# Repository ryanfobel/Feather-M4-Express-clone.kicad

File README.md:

# Feather-M4-Express-PCB-clone
KiCad version of Adafruit's [Feather M4 Express PCB](https://github.com/adafruit/Adafruit-Feather-M4-Express-PCB)
design files. Conversion from Eagle was performed using [these eagle-to-kicad scripts](https://github.com/lachlanA/eagle-to-kicad).

For more details on Adafruit's Feather M4 Express, check out the product pages at

   * https://www.adafruit.com/products/3857

Adafruit invests time and resources providing this open source design, 
please support Adafruit and open-source hardware by purchasing 
products from Adafruit!

Designed by Adafruit Industries.  
Creative Commons Attribution, Share-Alike license, check license.txt for more information.  
All text above must be included in any redistribution.  
Conversion from Eagle to KiCad by Ryan Fobel.

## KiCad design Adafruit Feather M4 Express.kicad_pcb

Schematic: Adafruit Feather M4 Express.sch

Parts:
C2, C4: 22pF; MICROBUILDER_0603-NO; MPN C0201C220K3GACTU
C3, C6, C8: 10~F; MICROBUILDER_0805-NO; MPN C0805C106K8PACTU
C5, C13: 10uF; MICROBUILDER_0805-NO; MPN C0805C106K8PACTU
C7, C10, C11, C12, C14, C15: 1uF; MICROBUILDER_0603-NO; MPN CL10B105KP8NNNC
CHG40: ORANGE; MICROBUILDER_CHIPLED_0805_NOOUTLINE; MPN LTST-C170KFKT
D4: MBR120; MICROBUILDER_SOD-123; MPN MBR120VLSFT3G
D+40: TPB1,27; TESTPAD_B1_27
D-40: TPB1,27; TESTPAD_B1_27
JP1: MICROBUILDER_1X16_ROUND
JP2, JP4: GROVE_HEADER_1X4; GROVE_HEADER_1x4
JP3: MICROBUILDER_1X12_ROUND
L2: 10uH; MICROBUILDER_INDUCTOR_1007; MPN LBR2518T100K
L40: RED; MICROBUILDER_CHIPLED_0805_NOOUTLINE; MPN 150060RS75000
LED1: WS2812B3535; MICROBUILDER_LED3535; MPN WS2812B3535
Q3: DMG341; MICROBUILDER_SOT23-R; MPN DMG3413L-7
R2: 1K; MICROBUILDER_0603-NO; MPN CRCW02011K00JNED
R3, R4, R5, R6, R8: 10K; MICROBUILDER_0603-NO; MPN ERJ-3GEYJ103V
R7: 2.2K; MICROBUILDER_0603-NO; MPN ERJ-3GEYJ222V
R9: 100K; MICROBUILDER_RESPACK_4X0603_NO; MPN ESR03EZPJ104
SJ1: MICROBUILDER_SOLDERJUMPER_CLOSEDWIRE
SW1: KMR2; MICROBUILDER_BTN_KMR2_4.6X2.8; MPN KMR231NG LFS
TP1, TP2: MICROBUILDER_TESTPOINT_ROUND_1.5MM
U1: 2MB Flash; MICROBUILDER_USON8; MPN GD25Q16CTIGR
U2: AP2112-3.3; MICROBUILDER_SOT23-5; MPN AP2112K-3.3TRG1
U3: MCP73831T-2ACI/OT; MICROBUILDER_SOT23-5; MPN MCP73831T-2ACI/OT
U$14: ATSAMD51J; MICROBUILDER_PQFN64-1; MPN ATSAMD51G19A-MU
VP_0, VP_1, VP_2, VP_3, VP_4, VP_5, VP_6, VP_7, VP_8, VP_9, VP_10, VP_11, VP_12: VPDEV0; VPAD_VPAC0
VP_13, VP_14, VP_15, VP_16, VP_17, VP_18, VP_19, VP_20, VP_21, VP_22, VP_23, VP_24, VP_25, VP_26, VP_27, VP_31, VP_32: VPDEV1; VPAD_VPAC1
VP_28, VP_29, VP_30, VP_33, VP_34, VP_35, VP_36, VP_37, VP_38, VP_39, VP_40, VP_41, VP_42, VP_43, VP_44, VP_45, VP_46, VP_47, VP_48, VP_49, VP_50, VP_51, VP_52, VP_53, VP_54, VP_55, VP_56, VP_57: VPDEV2; VPAD_VPAC2
X1: JSTPH; MICROBUILDER_JSTPH2; MPN S2B-PH-SM4-TB(LF)(SN)
X2: 32.768; ADAFRUIT2_XTAL3215; MPN LFXTAL009678REEL
X3: microUSB; MICROBUILDER_4UCONN_20329_V2; MPN 10118194-0001LF

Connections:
+3V3: C5.1, C7.1, C8.1, C10.1, C11.1, JP1.15, JP2.3, JP4.3, LED1.2 (VDD), R4.1, R5.2, R6.1, SJ1.2, U1.8 (VCC), U2.5 (OUT), U$14.8 (VDDANA), U$14.16 (PA07/I7/AIN7/SERCOM0.3), U$14.21 (VDDIO_0), U$14.34 (VDDIO_1), U$14.48 (VDDIO_2), U$14.56 (VDDIO_3)
A0: JP1.12, JP2.1, U$14.3 (PA02/EINT2/AIN0/VOUT0)
A1: JP1.11, JP2.2, U$14.14 (PA05/I5/AIN5/VOUT1/SERCOM0.1)
A2: JP1.10, U$14.11 (PB08/I8/AIN2/SERCOM4.0)
A3: JP1.9, U$14.12 (PB09/I9/AIN3/SERCOM4.1)
A4: JP1.8, U$14.13 (PA04/I4/VREFB/AIN4/SERCOM0.0)
A5: JP1.7, U$14.15 (PA06/I6/VREFC/AIN6/SERCOM0.2)
AREF: C14.1, JP1.14, SJ1.1, U$14.4 (PA03/I3/VREFA/AIN1)
D4: JP1.1, U$14.31 (PA14/I14/SERCOM2+4.2)
D5: JP3.10, U$14.35 (PA16/I2C/I0/SERCOM1.0+3.1)
D6: JP3.9, U$14.37 (PA18/I2/SERCOM1+3.2)
D8_NEOPIX: LED1.1 (DI), U$14.64 (PB03/I3/AIN15/SERCOM5.1)
D9: JP3.8, U$14.38 (PA19/I3/SERCOM1+3.3)
D10: JP3.7, U$14.41 (PA20/I4/SERCOM3+5.2/I2SFS0)
D11: JP3.6, U$14.42 (PA21/I5/SERCOM3+5.3/I2SDO)
D12: JP3.5, U$14.43 (PA22/I2C/16/SERCOM3.0+5.1/I2SDI)
D13: JP3.4, R7.1, U$14.44 (PA23/I2C/I7/SERCOM3.1+5.0/SOF/I2SFS1)
D+: D+40.TP, U$14.46 (PA25/19/SERCOM3+5.3/D+), X3.D+
D-: D-40.TP, U$14.45 (PA24/I8/SERCOM3+5.2/D-), X3.D-
EN: JP3.2, R3.1, U2.3 (EN)
GND: C2.2, C3.2, C4.2, C5.2, C6.2, C7.2, C8.2, C10.2, C11.2, C12.1, C13.2, C14.2, C15.2, JP1.13, JP2.4, JP4.4, L40.C, LED1.4 (GND), R8.2, R9.3 (1), R9.7 (2), SW1.B (S), SW1.B' (S1), U1.4 (VSS), U2.2 (GND), U3.2 (VSS), U$14.7 (GND_0), U$14.22 (GND_1), U$14.33 (GND_2), U$14.47 (GND_3), U$14.54 (GND_4), U$14.EXP (GND_0), VP_0.VP, VP_1.VP, VP_2.VP, VP_3.VP, VP_4.VP, VP_5.VP, VP_6.VP, VP_7.VP, VP_8.VP, VP_9.VP, VP_10.VP, VP_11.VP, VP_12.VP, VP_13.VP, VP_14.VP, VP_15.VP, VP_16.VP, VP_17.VP, VP_18.VP, VP_19.VP, VP_20.VP, VP_21.VP, VP_22.VP, VP_23.VP, VP_24.VP, VP_25.VP, VP_26.VP, VP_27.VP, VP_28.VP, VP_29.VP, VP_30.VP, VP_31.VP, VP_32.VP, X1.1, X3.BASE (GND), X3.GND, X3.SPRT (GND)
MISO: JP1.4, U$14.49 (PB22/I6/SERCOM1+5.2)
MOSI: JP1.5, U$14.50 (PB23/I7/SERCOM1+5.3)
unnamed: CHG40.C, R2.1
unnamed: L40.A, R7.2
unnamed: R2.2, U3.1 (STAT)
unnamed: R8.1, U3.5 (PROG)
unnamed: C2.1, U$14.1 (PA00/EINT0/SERCOM1.0), X2.P$1
unnamed: C4.1, U$14.2 (PA01/EINT1/SERCOM1.1), X2.P$2
unnamed: L2.P$2 (2), U$14.55 (VSW)
QSPI_CS: R5.1, U1.1 (SSEL), U$14.24 (PB11/I11/SERCOM4.3/I2SFS1)
QSPI_DATA[0]: U1.5 (MOSI), U$14.17 (PA08/I2C/AIN8/SERCOM0.0+2.1/I2SMCK)
QSPI_DATA[1]: U1.2 (MISO), U$14.18 (PA09/I2C/I9/AIN9/SERCOM0.1+2.0/I2SFS0)
QSPI_DATA[2]: U1.3 (WP#/IO2), U$14.19 (PA10/I10/AIN10/SERCOM0+2.2/I2SCK)
QSPI_DATA[3]: U1.7 (HOLD#/IO3), U$14.20 (PA11/I11/AIN11/SERCOM0+2.3/I2SDO)
QSPI_SCK: U1.6 (SCK), U$14.23 (PB10/I10/SERCOM4.2/I2SDI)
RX_D0: JP1.3, U$14.40 (PB17/SERCOM5.1/I2SMCK0)
SCK: JP1.6, U$14.36 (PA17/I2C/I1/SERCOM1.1+3.0)
SCL: JP3.11, JP4.1, U$14.30 (PA13/I13/I2C/SERCOM2.1+4.0)
SDA: JP3.12, JP4.2, U$14.29 (PA12/I12/I2C/SERCOM2.0+4.1)
SWCLK: R6.2, TP1.P$1, U$14.57 (PA30/I14/SERCOM1.2/SWCLK)
SWDIO: TP2.P$1, U$14.58 (PA31/I15/SERCOM1.3/SWDIO)
TX_D1: JP1.2, U$14.39 (PB16/I0/SERCOM5.0/I2SCK0)
VBAT: C3.1, JP3.1, Q3.3 (D), R9.8 (2), U3.3 (VBAT), X1.2
VBUS: CHG40.A, D4.A, JP3.3, Q3.1 (G), R9.6 (2), U3.4 (VDD), X3.VBUS
VDDCORE1: C13.1, C15.1, L2.P$1 (1), U$14.53 (VDDCORE)
VHI: C6.1, D4.C, Q3.2 (S), R3.2, U2.1 (IN)
V_DIV: R9.1, R9.2 (1), U$14.62 (PB01/I1/AIN13/SERCOM5.3)
~RESET: C12.2, JP1.16, R4.2, SW1.A, SW1.A' (P1), U$14.52 (~RESET)

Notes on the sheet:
POWER AND FILTERING
RESET
10K = 100mA
5.0K = 200mA
2.0K = 500mA
1.0K = 1000mA
USB AND BATTERY CHARGING
BREAKOUTS
RED LED
PCCDEN1
PCCDEN2
PCCD0
PCCD1
PCCD2
PCCD3
PCCD4
PCCD5
PCCD6
PCCD7
PCCLK
PCC: DEN1: SDA DEN2: SCL CLK: D6 D0: D11 D1: D13 D2: D10 D3: D12 D4: MISO D5: D5 D6: MOSI D7: SCK SPI: SERCOM1 DOPO = 0x3, SCK.1 & MO.3, MI.2 I2C: SERCOM2 or 4 UART: SERCOM5, TX on .0 & RX on .1 SPI Flash: QSPI (dual io) I2S: SCK0: A2 FS0: MISO SDI: MOSI SDO: D5 TCC1: WO0: D11 WO1: D13 WO2: D10 WO3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
CAN0_TX
CAN0_RX
DAC0
DAC1
CAN1_TX
CAN1_RX
R8 VALUE

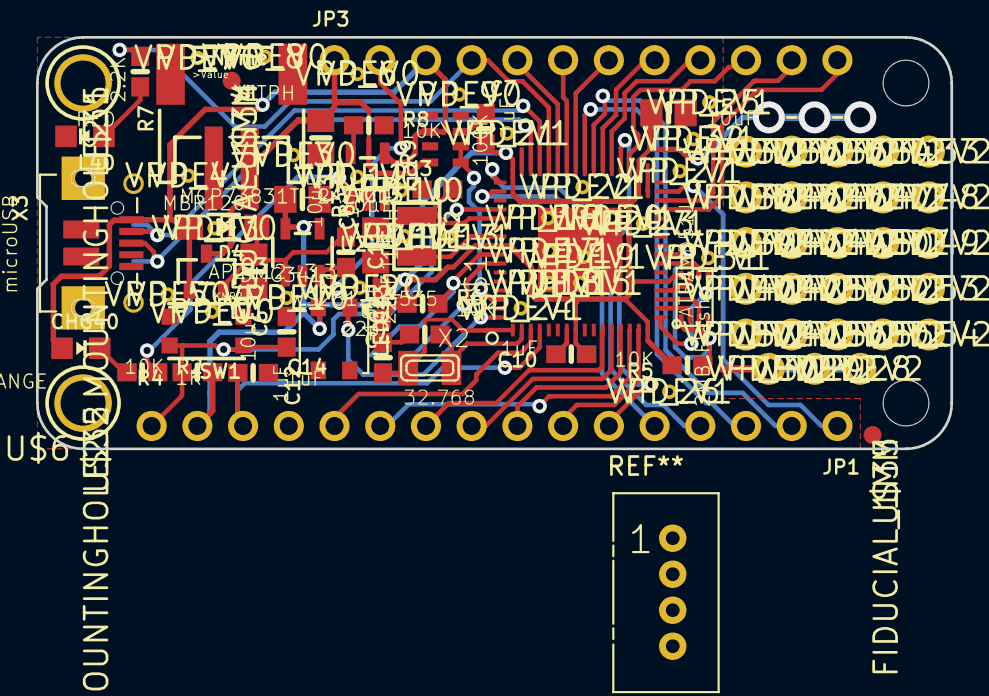
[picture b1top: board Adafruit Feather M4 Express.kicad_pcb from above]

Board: 2 copper layers, 50.8 x 22.9 mm, 109 parts (0 on the bottom side), 49 nets.

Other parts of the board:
@HOLE0, @HOLE1: (no value)
U$5: FEATHERM4_BOT
U$6: FEATHERM4_TOP
U$13: PCBFEAT-REV-040
U$31, U$32: MOUNTINGHOLE2.5; MOUNTINGHOLE_2.5_PLATED
U$34, U$35: FIDUCIAL_1MM

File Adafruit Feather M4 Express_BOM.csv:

Reference,Value,Footprint,Count,Datasheet,MPN
"C2, C4",22pF,MICROBUILDER_0603-NO,5,,C0201C220K3GACTU
"C3, C5, C6, C8, C13",10uF,MICROBUILDER_0805-NO,15,,C0805C106K8PACTU
"C7, C10, C11, C12, C14, C15",1uF,MICROBUILDER_0603-NO,21,,CL10B105KP8NNNC
CHG40,ORANGE,MICROBUILDER_CHIPLED_0805_NOOUTLINE,1,,LTST-C170KFKT
"D+40, D-40","TPB1,27",TESTPAD_B1_27,5,,
D4,MBR120,MICROBUILDER_SOD-123,1,,MBR120VLSFT3G
JP1,~,MICROBUILDER_1X16_ROUND,1,,
JP3,~,MICROBUILDER_1X12_ROUND,1,,
L2,10uH,MICROBUILDER_INDUCTOR_1007,1,,LBR2518T100K
L40,RED,MICROBUILDER_CHIPLED_0805_NOOUTLINE,1,,150060RS75000
LED1,WS2812B3535,MICROBUILDER_LED3535,1,,WS2812B3535
Q3,DMG341,MICROBUILDER_SOT23-R,1,,DMG3413L-7
R2,1K,MICROBUILDER_0603-NO,1,,CRCW02011K00JNED
"R3, R4, R5, R6, R8",10K,MICROBUILDER_0603-NO,16,,ERJ-3GEYJ103V
R7,2.2K,MICROBUILDER_0603-NO,1,,ERJ-3GEYJ222V
R9,100K,MICROBUILDER_RESPACK_4X0603_NO,1,,ESR03EZPJ104
SJ1,~,MICROBUILDER_SOLDERJUMPER_CLOSEDWIRE,1,,
SW1,KMR2,MICROBUILDER_BTN_KMR2_4.6X2.8,1,,KMR231NG LFS
"TP1, TP2",~,MICROBUILDER_TESTPOINT_ROUND_1.5MM,5,,
U$14,ATSAMD51J,MICROBUILDER_PQFN64-1,1,,ATSAMD51G19A-MU
U1,2MB Flash,MICROBUILDER_USON8,1,,GD25Q16CTIGR
U2,AP2112-3.3,MICROBUILDER_SOT23-5,1,,AP2112K-3.3TRG1
U3,MCP73831T-2ACI/OT,MICROBUILDER_SOT23-5,1,,MCP73831T-2ACI/OT
"VP_0, VP_1, VP_2, VP_3, VP_4, VP_5, VP_6, VP_7, VP_8, VP_9, VP_10, VP_11, VP_12",VPDEV0,VPAD_VPAC0,49,,
"VP_13, VP_14, VP_15, VP_16, VP_17, VP_18, VP_19, VP_20, VP_21, VP_22, VP_23, VP_24, VP_25, VP_26, VP_27, VP_31, VP_32",VPDEV1,VPAD_VPAC1,65,,
"VP_28, VP_29, VP_30, VP_33, VP_34, VP_35, VP_36, VP_37, VP_38, VP_39, VP_40, VP_41, VP_42, VP_43, VP_44, VP_45, VP_46, VP_47, VP_48, VP_49, VP_50, VP_51, VP_52, VP_53, VP_54, VP_55, VP_56, VP_57",VPDEV2,VPAD_VPAC2,109,,
X1,JSTPH,MICROBUILDER_JSTPH2,1,,S2B-PH-SM4-TB(LF)(SN)
X2,32.765,ADAFRUIT2_XTAL3215,1,,LFXTAL009678REEL
X3,microUSB,MICROBUILDER_4UCONN_20329_V2,1,,10118194-0001LF

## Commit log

2018-09-11 Initial conversion
2018-09-11 Resize schematic
2018-09-11 Add gitignore, BOM
2018-09-11 Update BOM and add MPN to schematic parts
2018-09-11 Add README
2018-09-11 Fix product link
2018-09-13 Attempted to add Grove header
    Got the schematic tidied up, and added Grove header to schematic.
    When I went to run the footprint association it broke because the footprint file is .mod, which is legacy and not supported :(
2018-09-16 Major update to board and GND pads
    Added the Grove connectors.
    Had to edit settings for the GND pads so that they tied to the copper pour with 'solid' instead of 'spokes' so that the pour areas would connect more. Also had to redefine the USB connector pins so t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
2018-09-17 finished routing
    Got the grove connections routed, and passing DRC
2018-09-18 added process images
2018-09-19 Added production process files from PCB pool
2019-09-26 just opened in the new KiCad and all the symbols are there
